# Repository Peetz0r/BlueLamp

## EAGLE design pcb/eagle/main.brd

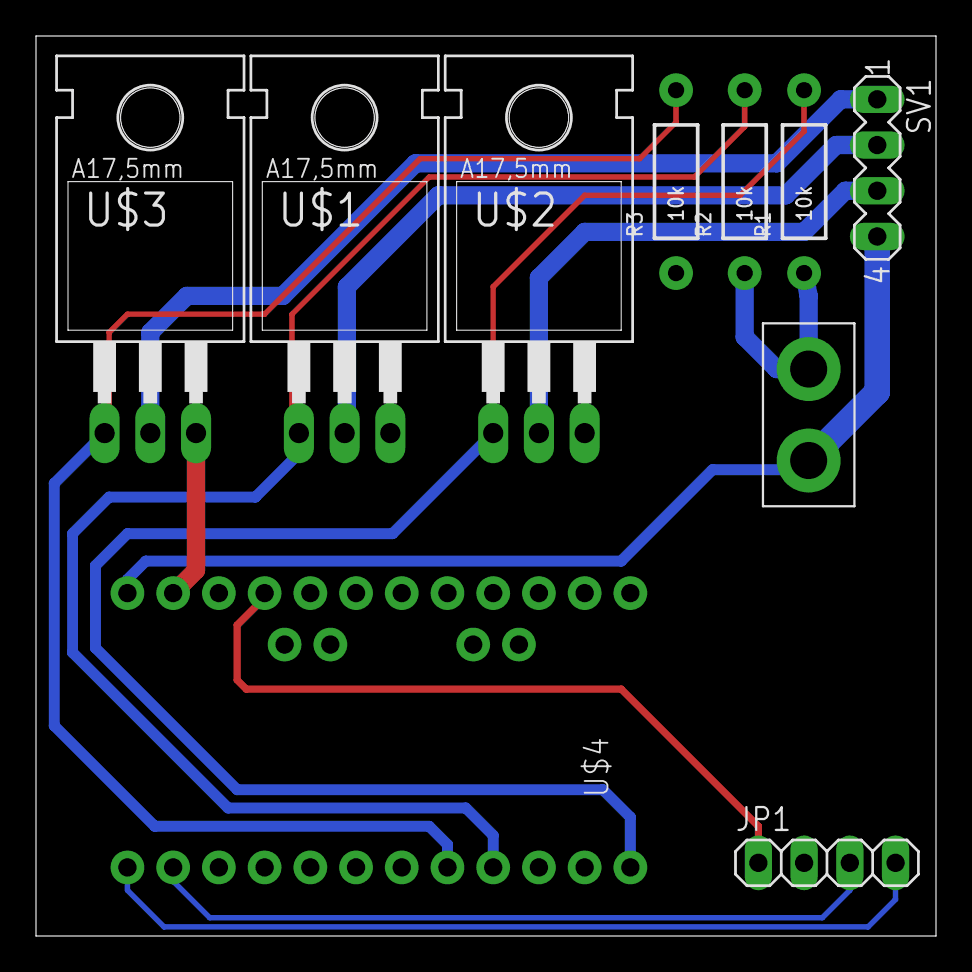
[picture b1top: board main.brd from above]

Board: 2 copper layers, 50.0 x 50.0 mm, 10 parts (0 on the bottom side), 11 nets.

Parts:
JP1: 1X04
JP2: M02PTH4; 1X02_XTRA_BIG
R1, R2, R3: 10k; AXIAL-0.4
SV1: MA04-1
U$1, U$2, U$3: IRL540; TO220AH
U$4: ARDUINO_PRO_MINI

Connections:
GND: JP1.2, JP2.2, R1.P$1, R2.P$1, R3.P$1, U$1.E, U$2.E, U$3.E, U$4.23
unnamed: R3.P$2, U$3.B, U$4.8
unnamed: R2.P$2, U$1.B, U$4.9
unnamed: R1.P$2, U$2.B, U$4.12
unnamed: JP2.1, SV1.4, U$4.24
unnamed: SV1.1, U$3.C
unnamed: SV1.3, U$2.C
unnamed: SV1.2, U$1.C
RX: JP1.4, U$4.1
TX: JP1.3, U$4.2
VCC: JP1.1, U$4.21

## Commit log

2014-10-06 Initial commit
    The Android app and Arduino sketch are mostly done now.
    PCB could be done, not sure at all.
2014-10-06 Change logging levels
2014-10-06 Update launcher icon
2014-10-06 Enable proguard
2014-10-06 Added more screenshots and other images
2014-10-06 Added some more screenshots Play Store requitements are quite heavy here
2014-10-06 Update pcb image
2014-10-06 Remove 100x50 version of pcb, final board is probably going to be 50x50 anyway
2014-10-09 Added signature verification
2014-10-09 add Eagle pcb design
2014-10-10 Remove and ignore Eagle backup files
2014-10-21 Update arduino project
2014-10-21 Update PCB design to single-sided
2014-11-24 Move sketch to it's own directory (to fix compatibility with the default-but-ugly Arduino IDE inotool seems to be fine with this
2014-11-24 Update PCB to fix pulldown resistor problem
2014-11-24 Change behaviour of spinner and togglebutton. Now, when changing the selected device address, the old connection will be closed, and it will attempt to connect to the newly selected address
    Also, recompile for Lollipop, with Material Design enabled for api 21+ devices
2014-11-24 Material Design screenshot added
2014-11-25 Made the app even better and even more user-friendly
2014-12-18 Update for Android Studio 1.0 release
2015-01-06 Removed silly textview
2015-04-23 Recompile for newer sdk (21 => 22) and add apk to github repo
2015-04-23 Oops, version number madness

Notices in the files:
parts and their libraries:
SparkFun-Boards: Licensing: Creative Commons ShareAlike 4.0 International - https://creativecommons.org/licenses/by-sa/4.0
